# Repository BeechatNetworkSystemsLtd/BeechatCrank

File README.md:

# Beechat Crank
## _The last charger you'll ever need_

Beechat Crank is a human-powered, open-hardware, fully-waterproof, electricity generator.
The project was born out of the need to power electronics in all off-grid scenarios. We needed a way to power our devices in all weather conditions, and making a human-powered generator meant that problem could be solved. When we looked for a solution, we didn't find what we were looking for, so we decided to make it, and make it open source!

## Features

- High power (3A) USB-C IPX8 output
- 18650 3600 mAh battery (LG M36)
- Charging time of 4 hrs 24 min. to full charge with 10% efficiency loss at 4.5 Watts.
- Overcharge protection

## Parts

1. Beechat Crank is composed of the main device, which we call the _Heart_. It contains the battery, the generator and all the electronics (the handle is detachable) :

2. The _Pedal Case_ is an assembly which the _Heart_ can be attached in. which dramatically speeds up the charging from 2.5 hours to 25-30 minutes. This is achieved with reduction gears to, with the same revolutions per minute, generate more electricity.

## _Generator_ part
We have chosen the 35L048B1B motor with a mass of 88 grams, giving us us 450 mA for each phase of the coil and works at 5V. 
The wire leads are connected via female Molex connectors to the charging PCB board.

## _Heart_ parts

| Part no. | Part name | Quantity | Description | Link | Price |
| ------ | ------ | ------ | ------ | ------ | ------ |
| 01 | Body | 1 | Injection molded ABS/PC |
| 02 |  Lid | 1 | Injection molded ABS/PC
| 03 | Handle | 1 | Injection molded ABS/PC
| 04 | Light pipe | 1 | Transparent injection molded PC
| 05 | Motor | 1 | | [Link](https://aliexpress.com/item/4000827045633.html?spm=a2g0o.productlist.0.0.23037dfaZSxbKX&algo_pvid=1a64035c-7bcb-481b-8e93-a88d612e990f&algo_expid=1a64035c-7bcb-481b-8e93-a88d612e990f-37&btsid=0bb0623916143291425175994eaa36&ws_ab_test=searchweb0_0,searchweb201602_,searchweb201603_) | $11
| 06 | Bearing | 1 | | [Link](http://manufacturer.ketanbearing.in/70745-NSKF686ADD-Bearing/) | $0.5
| 07 | PCB | 1 | |  | $6
| 08 | Battery holder | 1 | | [Link](https://aliexpress.com/item/4001063295116.html) | $0.09
| 09 | Lid O-Ring | 1 | | [Link]() | $0.95
| 10 | Bearing O-ring | 1 | | [Link](https://www.oringsandmore.com/silicone-o-rings-11-5-x-1mm-minimum-10-pcs/) | $0.08
| 10 | Adhesive | 1 | | | $8.36
| 11 | 10 mm M2 screws | 6 | | |
| 12 | 10 mm M3 screw | 1 | | |
|Total cost (excl. plastic parts and adhesive) | | | | | $18.62 

## _Heart_ PCB parts

All parts are under the "3_BOM and CPL" folder

## _Pedal Case_ parts

| Part no. | Part name | Quantity | Description | Link | Price |
| ------ | ------ | ------ | ------ | ------ | ------ |
| 01 | Sheet metal stand | 1 | Stainless steel sheet metal bend |
| 02 |  Plastic cover | 1 | Injection molded ABS plastic cover
| 03 | 20 teeth spur gear | 1 | Hardened steel-with M3 thread (Custom made)
| 04 | 30/12 teeth double spur gear | 1 | Hardened steel (Custom made)
| 05 | 48 teeth spur gear | 1 | Hardened steel (Custom made)
| 06 | Left pedal crank Arm | 1 | Hardened steel with M8 thread (Custom made) | [Link](https://www.amazon.com/Electric-Bicycle-Conversion-Aluminum-crankset/dp/B083HWCMSR/ref=sr_1_2?dchild=1&keywords=Yosoo%2Bright%2Bcrank&qid=1618046572&sr=8-2&th=1)
| 07 | Right pedal crank Arm | 1 | Standard part
| 08 | UFL003 bearing | 2 | Standard part | [Link](https://es.aliexpress.com/item/1713738795.html?spm=a2g0o.productlist.0.0.2be33d737c2av2&algo_pvid=3cf454b2-064e-440d-981a-a02dd87b7819&algo_expid=3cf454b2-064e-440d-981a-a02dd87b7819-1&btsid=0bb47a1a16180471473202376e0cfd&ws_ab_test=searchweb0_0,searchweb201602_,searchweb201603_)
| 09 | 6mm hollow rod | 1 | with M3 internal thread(Custom made)
| 10 | M6 Washer | 2 | Standard part
| 11 | M3 Washer | 1 | Standard part
| 12 | M7 bolt | 4 | Standard part
| 13 | M3 bolt 15 mm | 3 | Standard part
| 14 | M3 bolt 8 mm | 3 | Standard part
| 15 | M7 nut | 4 | Standard part
| 16 | M3 nut | 3 | Standard part
| 17 | Pedal crank bolt | 2 | Standard part | [Link](https://www.sportwheels.ca/mtb-crank-bolt-crank-nut.html)
| 18 | Pedal | 2 | Standard part | [Link](https://www.amazon.com/BV-Universal-Bicycle-16-Inch-Spindle/dp/B01LYOB0M6/ref=sr_1_6?dchild=1&keywords=bike+pedal&qid=1618046767&sr=8-6) 

## Development

Want to contribute? Great!

Make a change in the files and create a pull request!

## License

**Open Source Hardware, Non-Commercial**

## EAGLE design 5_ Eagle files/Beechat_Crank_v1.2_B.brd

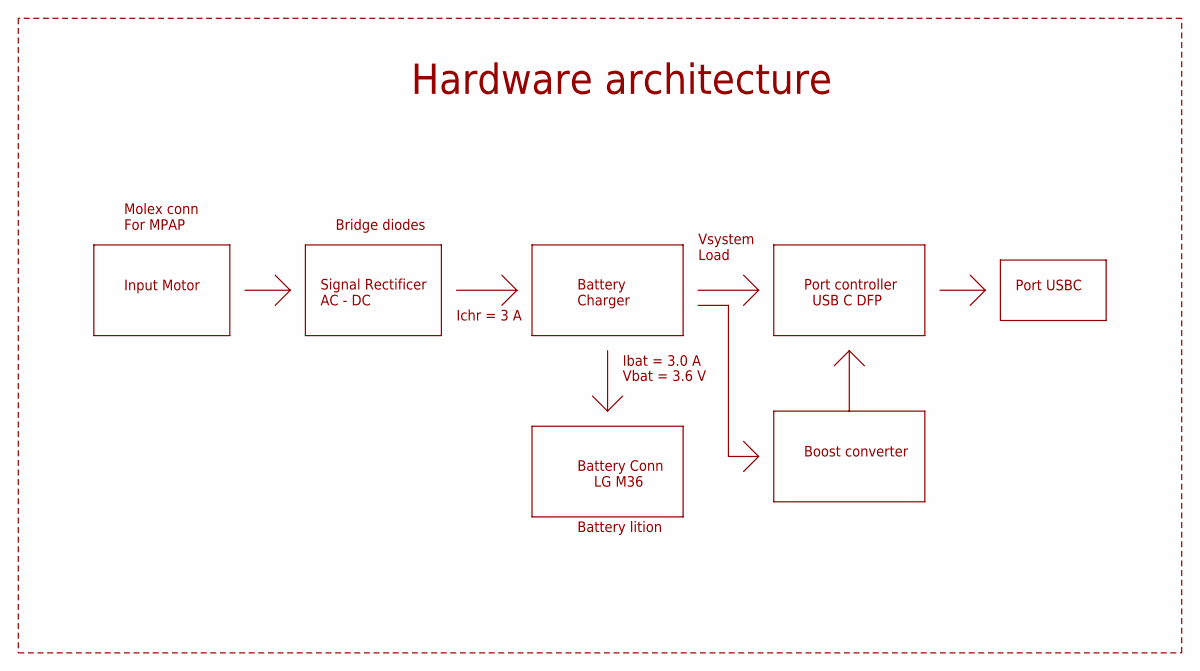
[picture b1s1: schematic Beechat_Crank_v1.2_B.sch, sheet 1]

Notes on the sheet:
Hardware architecture
Input Motor
Molex conn For MPAP
Signal Rectificer AC - DC
Bridge diodes
Battery Charger
Battery Conn LG M36
Ibat = 3.0 A
Ichr = 3 A
Battery lition
Vbat = 3.6 V
Port controller USB C DFP
Vsystem Load
Port USBC
Boost converter

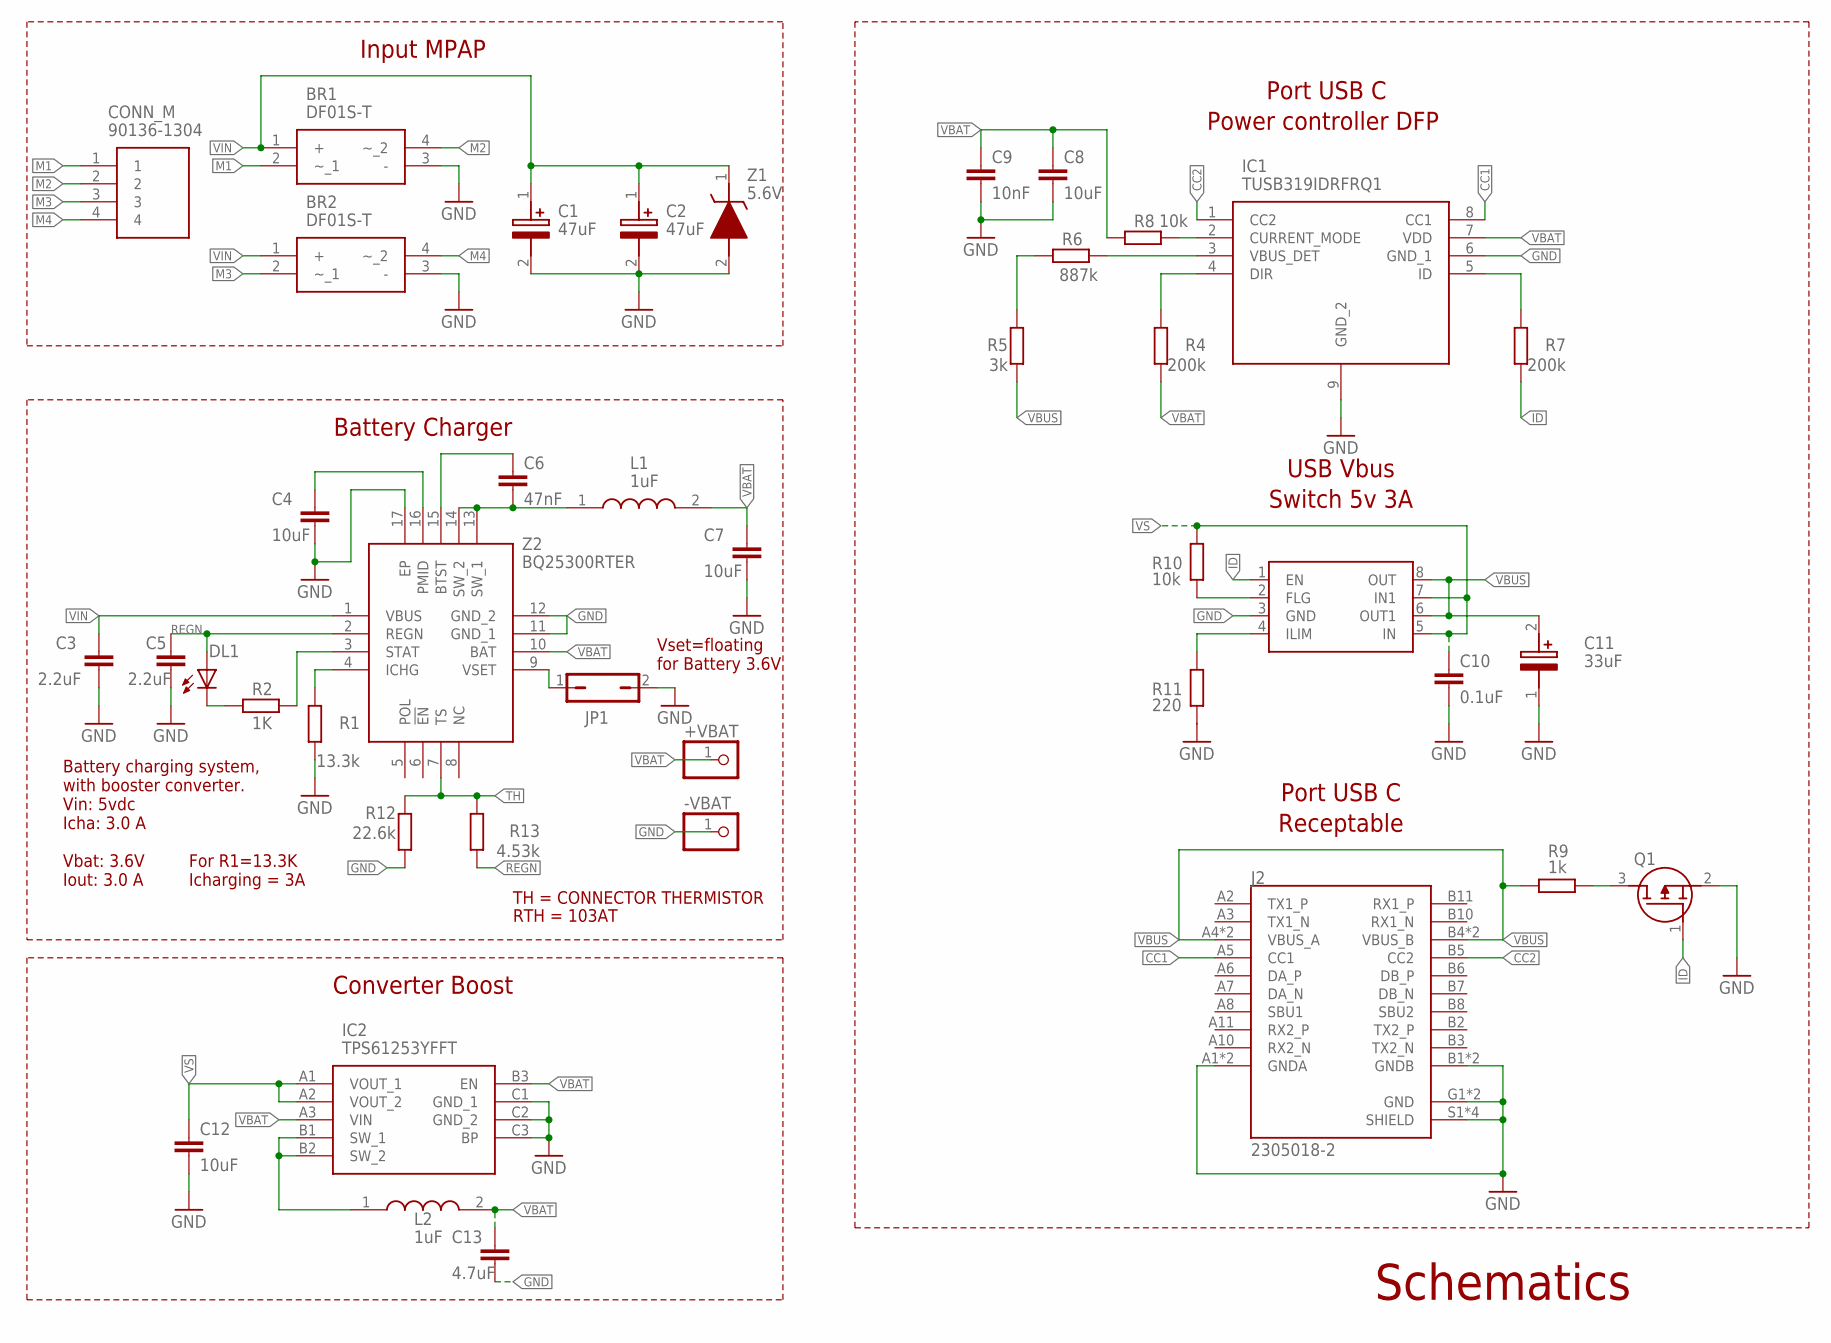
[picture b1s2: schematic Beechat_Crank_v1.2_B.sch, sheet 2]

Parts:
+VBAT: PINHD-1X1; 1X01
-VBAT: PINHD-1X1; 1X01
BR1, BR2: DF01S-T; SOP510P1040X293-4N
C1, C2: 47uF; CAPAE660X800N
C3, C5: 2.2uF; C0603
C4, C7: 10uF; C1210
C6: 47nF; C0603
C8, C12: 10uF; C0603
C9: 10nF; C0603
C10: 0.1uF; C0603
C11: 33uF; CAPAE660X550N
C13: 4.7uF; C0603
CONN_M: 90136-1304; SHDR4W65P0X254_1X4_1351X721X11
DL1: LED_BLUE; CHIP-LED0603
IC1: TUSB319IDRFRQ1; SON50P200X200X80-9N
IC2: TPS61253YFFT; BGA9C40P3X3_121X131X62
J2: 2305018-2; TE_2305018-2
JP1: JP1Q; JP1
L1, L2: 1uF; LQH5BPB100MT0L
Q1: SI2337DS-T1-BE3; SOT95P237X112-3N
R1: 13.3k; R0603
R2: 1K; R0603
R4, R7: 200k; R0603
R5: 3k; R0603
R6: 887k; R0603
R8, R10: 10k; R0603
R9: 1k; R0603
R11: 220; R0603
R12: 22.6k; R0603
R13: 4.53k; R0603
U$1: MIC2545; SOIC127P599X173-8N
Z1: 5.6V; SOD3716X135N
Z2: BQ25300RTER; QFN50P300X300X80-17N

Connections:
CC1: IC1.8 (CC1), J2.A5 (CC1)
CC2: IC1.1 (CC2), J2.B5 (CC2)
GND: -VBAT.1, BR1.3 (-), BR2.3 (-), C1.2 (-), C2.2 (-), C3.2, C4.2, C5.2, C7.2, C8.2, C9.2, C10.2, C11.1 (-), C12.2, C13.2, IC1.6 (GND_1), IC1.9 (GND_2), IC2.C1 (GND_1), IC2.C2 (GND_2), IC2.C3 (BP), J2.A1 (GNDA), J2.A12 (GNDA), J2.B1 (GNDB), J2.B12 (GNDB), J2.G1 (GND), J2.G2 (GND), J2.S1 (SHIELD), J2.S2 (SHIELD), J2.S3 (SHIELD), J2.S4 (SHIELD), JP1.2, Q1.2 (S), R1.1, R11.2, R12.1, U$1.3 (GND), Z1.2 (A), Z2.11 (GND_1), Z2.12 (GND_2), Z2.17 (EP)
ID: Q1.1 (G), R7.1, U$1.1 (EN)
M1: BR1.2 (~_1), CONN_M.1
M2: BR1.4 (~_2), CONN_M.2
M3: BR2.2 (~_1), CONN_M.3
M4: BR2.4 (~_2), CONN_M.4
unnamed: JP1.1, Z2.9 (VSET)
unnamed: R1.2, Z2.4 (ICHG)
unnamed: DL1.C, R2.2
unnamed: C4.1, Z2.16 (PMID)
unnamed: R2.1, Z2.3 (STAT)
unnamed: C6.1, Z2.15 (BTST)
unnamed: C6.2, L1.1, Z2.13 (SW_1), Z2.14 (SW_2)
unnamed: IC1.3 (VBUS_DET), R6.1
unnamed: R5.2, R6.2
unnamed: IC1.4 (DIR), R4.2
unnamed: IC1.5 (ID), R7.2
unnamed: R10.2, U$1.2 (FLG)
unnamed: IC1.2 (CURRENT_MODE), R8.1
unnamed: IC2.B1 (SW_1), IC2.B2 (SW_2), L2.1
unnamed: Q1.3 (D), R9.1
unnamed: R11.1, U$1.4 (ILIM)
REGN: C5.1, DL1.A, R13.1, Z2.2 (REGN)
TH: R12.2, R13.2, Z2.7 (TS)
VBAT: +VBAT.1, C7.1, C8.1, C9.1, C13.1, IC1.7 (VDD), IC2.A3 (VIN), IC2.B3 (EN), L1.2, L2.2, R4.1, R8.2, Z2.10 (BAT)
VBUS: C11.2 (+), J2.A4 (VBUS_A), J2.A9 (VBUS_A), J2.B4 (VBUS_B), J2.B9 (VBUS_B), R5.1, R9.2, U$1.6 (OUT1), U$1.8 (OUT)
VIN: BR1.1 (+), BR2.1 (+), C1.1 (+), C2.1 (+), C3.1, Z1.1 (K), Z2.1 (VBUS)
VS: C10.1, C12.1, IC2.A1 (VOUT_1), IC2.A2 (VOUT_2), R10.1, U$1.5 (IN), U$1.7 (IN1)

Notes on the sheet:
Input MPAP
Battery charging system, with booster converter. Vin: 5vdc Icha: 3.0 A Vbat: 3.6V Iout: 3.0 A
Battery Charger
Port USB C Receptable
USB Vbus Switch 5v 3A
Port USB C Power controller DFP
Schematics
For R1=13.3K Icharging = 3A
TH = CONNECTOR THERMISTOR
RTH = 103AT
Vset=floating for Battery 3.6V
Converter Boost

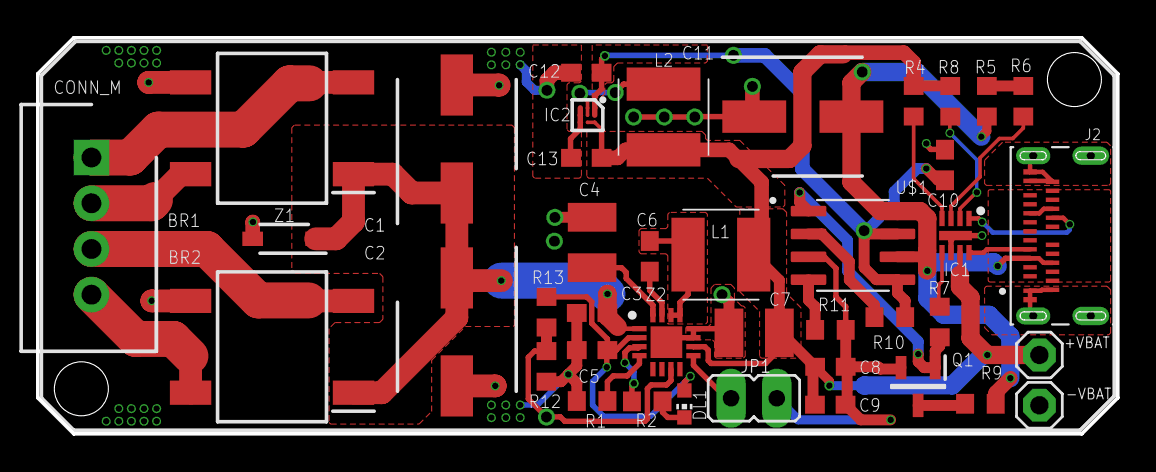
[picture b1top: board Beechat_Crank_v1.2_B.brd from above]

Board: 2 copper layers, 60.0 x 22.0 mm, 41 parts (0 on the bottom side), 30 nets.

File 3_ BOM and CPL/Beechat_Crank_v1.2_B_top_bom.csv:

Comment,Designator,Footprint,LCSC Part #
0.1uF,Q1 C10,C0603,
1K,R2,R0603,
1k,R9,R0603,
1uF,L1 L2,LQH5BPB100MT0L,
2.2uF,C3 C5,C0603,
3k,R5,R0603,
4.7uF,C13,C0603,
4.53k,R13,R0603,
5.6V,Z1,SOD3716X135N,
10k,R8 R10,R0603,
10nF,C9,C0603,
10uF,C4 C7,C1210,
10uF,C8 C12,C0603,
13.3k,R1,R0603,
22.6k,R12,R0603,
33uF,C11,CAPAE660X550N,
47nF,C6,C0603,
47uF,C1 C2,CAPAE660X800N,
200k,R4 R7,R0603,
220,R11,R0603,
887k,R6,R0603,
2305018-2,J2,TE_2305018-2,
BQ25300RTER,Z2,QFN50P300X300X80-17N,
DF01S-T,BR1 BR2,SOP510P1040X293-4N,
LED_BLUE,DL1,CHIP-LED0603,
MIC2545,U$1,SOIC127P599X173-8N,
TPS61253YFFT,IC2,BGA9C40P3X3_121X131X62,
TUSB319IDRFRQ1,IC1,SON50P200X200X80-9N,

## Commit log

2021-04-30 Added Assembly Process PDF
2021-11-04 Beechat Crank V1.2 Update
    We can now configure the voltage of the battery that we want to use, by default the chosen LG M36 battery provides 3.6v 3A, but then with a jumper we can configure the value and change the battery if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
